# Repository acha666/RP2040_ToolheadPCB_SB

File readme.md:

# Stealthburner_Toolhead_PCB

<font size=5>[中文文档/Chinese Document](readme_cn.md)</font>

## Overview
This project contains a 3Dprinter Toolhead PCB for VORON StealthBurner Toolhead

The board has

* RP2040 Microcontroller, connect to Raspberry PI with USB
* TMC2209 for extruder motor
* MAX31865 RTD-to-Digital Converter
* Si7021/HTU21D humidity&temperature sensor
* ADXL345 accrometer
* Two 5pins fan connecter, fit with 2/3/4 wires, 12/24V fans
* A 3pins probe connecter
* A normal NTC Thermistor connector
* A 2pins X Endstop connector
* A 3pins 5V WS2812(Neopixel) LED connector
* A 24V heater connector

## [Config Referencce](klipper_config.cfg)

## [Programming Guide](Document/programming.md)

## Details
### Microcontroller
You can easily buy a RP2040 chip by about 1USD, it's much cheaper than similar STM32 series MCU today

the RP2040 has some UART interfaces and a USB port, the USB is used for this design

### MAX31865
the on-board MAX31865 chip supports 2/3/4 wires, PT100/PT1000 RTD. please notice that you should choose the reference resistor(430R/4.3K) and a capacitor(100nF/1uF) based on your RTD value. If you use an 3wire RTD, please connect the FORCE2 pin to PORCE+, otherwise connect it to GND. Please make sure that your wiring is correct. Check the [Datasheet](https://datasheets.maximintegrated.com/en/ds/MAX31865.pdf) and [Here](Document/max31865.md) for more information.

### Si7021
This sensor is used to monitor chamber temp.

DS18B20 sensors are only supported on the "host mcu". A NTC thermistor should work too, so if a RTD sensor is used to measure hotend temp, you can have a try.

### ADXL345
is for resonances measurement. Both ADXL343 and ADXL345 should work

### FAN Connecter
support 2wires, 3wires(with speed monitor pin), 4wires(with PWM input and speed monitor)

12V/24V voltage can be set by the jumper. Check [Here](Document/fan.md) for more information.

If using 12V fan, be careful that the current required by the fan must not exceed the maximum current that the DC-DC can provide.

### Neopixel LED
The 5V on the board is the LDO output, the output current is limited, and too many lamp beads cannot be connected in series.

### Heater
be careful about selection on MOSFET, a N-Channel MOSFET with low RDSon at 4.5V

### DC-DC
many models can be used, as long as they have same pin out

The inductor is 4x4mm package, as slim as possible(under 2mm height)

**Inductor Options**
* WPN4012H (Sunlord)
* SPH4012S PH4018 (Sunlord)
* SWPA4010 SWPA4018 SWPA4020 (Sunlord)
* SLW4010 (Sunltech)
* FHD4012 (cjiang)

**Buck converter options**
* LMR14006
* LMR14010
* LMR54410(not tested)
* MP2451(not tested)
* ~~BL9342(not recommended)~~

please check the schmatic and chip datasheet for more details

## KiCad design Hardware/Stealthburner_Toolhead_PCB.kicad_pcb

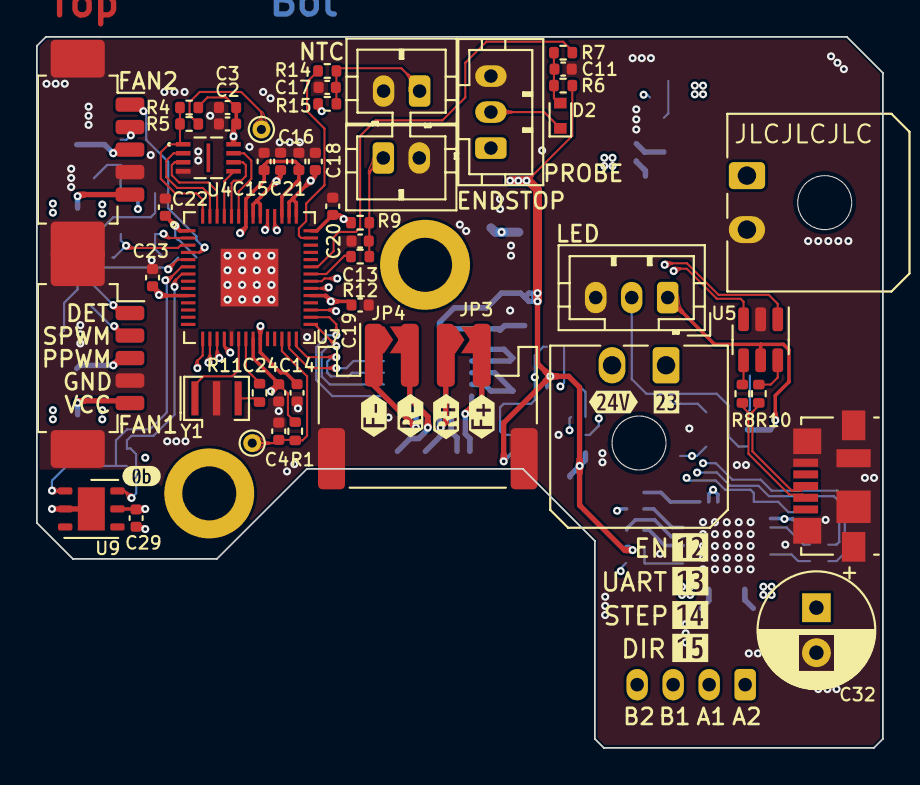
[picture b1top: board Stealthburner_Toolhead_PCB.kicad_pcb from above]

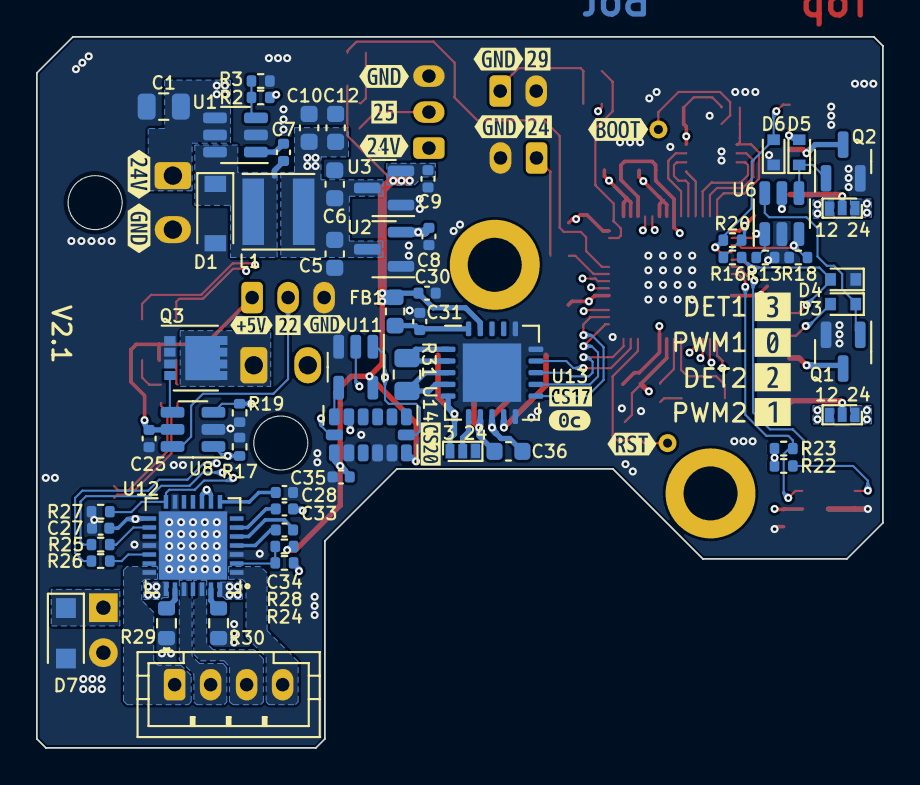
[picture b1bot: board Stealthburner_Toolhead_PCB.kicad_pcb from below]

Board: 4 copper layers, 47.0 x 39.5 mm, 143 parts (80 on the bottom side), 83 nets.

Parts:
C1: 22uF/35V; C_0805_2012Metric
C2: 2.2uF; C_0402_1005Metric
C3, C4, C7, C11, C13, C14, C15, C19, C20, C21, C22, C23, C24, C25, C27, C29, C30, C31, C33, C35: 100nF; C_0402_1005Metric
C5, C6: 10uF; C_0603_1608Metric
C8, C9, C17: 10uF; C_0402_1005Metric
C10, C12: 22uF; C_0603_1608Metric
C16, C18: 1uF; C_0402_1005Metric
C28: 4.7uF; C_0402_1005Metric
C32: 100uF; CP_Radial_D6.3mm_P2.50mm
C34: 22nF; C_0402_1005Metric
C36: 100nF/1uF; C_0603_1608Metric
D1: SS14L; D_SOD-123
D2: 1N4148WT; D_SOD-523
D3, D5: 1N4148; D_SOD-523
D4, D6: D_TVS; D_SOD-523
D7: SMF28A; D_SOD-123F
FB1: 120R@100MHz; L_0603_1608Metric
H1, H2: MountingHole; MountingHole_3mm_Pad
J1, J9: Conn_01x02; Molex_Micro-Fit_3.0_43650-0200_1x02_P3.00mm_Horizontal
J2, J8: Conn_01x03; JST_PH_B3B-PH-K_1x03_P2.00mm_Vertical
J3: TestPoint; TestPoint_THTPad_D1.0mm_Drill0.5mm
J4, J6: Conn_01x02; JST_PH_B2B-PH-K_1x02_P2.00mm_Vertical
J5: USB_B_Micro; USB_Micro-B_Molex_47346-0001
J7, J10: Conn_01x05; Molex_PicoBlade_53261-0571_1x05-1MP_P1.25mm_Horizontal
J11: Conn_01x04; JST_PH_S4B-PH-SM4-TB_1x04-1MP_P2.00mm_Horizontal
J12: Conn_01x04; JST_PH_B4B-PH-K_1x04_P2.00mm_Vertical
JP1, JP2: SolderJumper_3_Open; SolderJumper-3_P1.3mm_Open_Pad1.0x1.5mm
JP3, JP4: SolderJumper_2_Open; SolderJumper-2_P1.3mm_Open_TrianglePad1.0x1.5mm
JP5: 1_Library:SolderJumper-3_P1.3mm_Open_Pad1.0x1.5mm; SolderJumper-3_P1.3mm_Open_Pad1.0x1.5mm
L1: 6.2uH; L_Taiyo-Yuden_NR-40xx
Q1, Q2: AO3400A; SOT-23
Q3: WSD4038DN; VSON-8_3.3x3.3mm_P0.65mm_NexFET
R1, R6, R9, R13, R16, R17, R18, R19, R20, R22, R23: 10K; R_0402_1005Metric
R2: 309K; R_0402_1005Metric
R3: 22.1K; R_0402_1005Metric
R4: NC; R_0402_1005Metric
R5, R11: 1K; R_0402_1005Metric
R7, R12, R14, R24, R25, R26: 100R; R_0402_1005Metric
R8, R10: 27R; R_0402_1005Metric
R15: 4.7K; R_0402_1005Metric
R27, R28: 20K; R_0402_1005Metric
R29, R30: 0R11; R_0603_1608Metric
R31: 430R/4.3K; R_0805_2012Metric
TP1: TestPoint; TestPoint_THTPad_D1.0mm_Drill0.5mm
U1: LMR54410; SOT-23-6
U2: ME6209A50M3G; SOT-23
U3: ME6209A33M3G; SOT-23
U4: W25Q16JVUXIQ_WIN; W25Q16JVUXIQ
U5: USBLC6-2SC6; SOT-23-6
U6, U8: 74LVC2G17; SOT-23-6
U7: RP2040; RP2040TR7
U9: Si7021-A20; DFN-6-1EP_3x3mm_P1mm_EP1.5x2.4mm
U11: 74LVC1G32; SOT-23-5
U12: QFN28_5X5_3X8_EPAD_TRI; TMC2209-LA-T
U13: MAX31865xTP; TQFN-20-1EP_5x5mm_P0.65mm_EP3.25x3.25mm
U14: ADXL343; LGA-14_3x5mm_P0.8mm_LayoutBorder1x6y
Y1: CSTNE12M0; Resonator_SMD_Murata_CSTxExxV-3Pin_3.0x1.1mm
kibuzzard-62BB1C3A: G***; kibuzzard-62BB1C3A
kibuzzard-62BB1DD3: G***; kibuzzard-62BB1DD3
kibuzzard-62BB1FE0: G***; kibuzzard-62BB1FE0
kibuzzard-62BB1FE5: G***; kibuzzard-62BB1FE5
kibuzzard-62BB1FE8: G***; kibuzzard-62BB1FE8
kibuzzard-62BB1FEC: G***; kibuzzard-62BB1FEC
kibuzzard-62BB2156: G***; kibuzzard-62BB2156
kibuzzard-62BB2169: G***; kibuzzard-62BB2169
kibuzzard-62BB2226, kibuzzard-62BB2226#2, kibuzzard-62BB2226#3: G***; kibuzzard-62BB2226
kibuzzard-62BB2232, kibuzzard-62BB2232#2, kibuzzard-62BB2232#3, kibuzzard-62BB2232#4: G***; kibuzzard-62BB2232
kibuzzard-62BB2280: G***; kibuzzard-62BB2280
kibuzzard-62BD8A5A: G***; kibuzzard-62BD8A5A
kibuzzard-62BD8A5E: G***; kibuzzard-62BD8A5E
kibuzzard-62BD8A50: G***; kibuzzard-62BD8A50
kibuzzard-62BD8A57: G***; kibuzzard-62BD8A57
kibuzzard-62BD8C8D: G***; kibuzzard-62BD8C8D
kibuzzard-62BD8C64: G***; kibuzzard-62BD8C64
kibuzzard-62BD8846: G***; kibuzzard-62BD8846
kibuzzard-62E7C93B: G***; kibuzzard-62E7C93B
kibuzzard-62E7C936: G***; kibuzzard-62E7C936
kibuzzard-62E7C943: G***; kibuzzard-62E7C943
kibuzzard-62E7C964: G***; kibuzzard-62E7C964
kibuzzard-62F0BBF4: G***; kibuzzard-62F0BBF4
kibuzzard-6309F118: G***; kibuzzard-6309F118
kibuzzard-63148E7F: G***; kibuzzard-63148E7F
kibuzzard-63148E89: G***; kibuzzard-63148E89
kibuzzard-63148E96: G***; kibuzzard-63148E96

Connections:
+1V1: C14.1, C15.1, C16.1, U7.23 (DVDD), U7.45 (VREG_VOUT), U7.50 (DVDD)
+3V3: C2.1, C3.1, C9.1, C18.1, C19.1, C20.1, C21.1, C22.1, C23.1, C24.1, C27.2, C29.1, C30.1, C35.1, FB1.1, R1.1, R4.1, R6.1, R9.1, R15.1, R16.1, R20.1, R22.1, R23.1, R28.1, U3.2 (OUT), U4.8 (VCC), U7.1 (IOVDD), U7.10 (IOVDD), U7.22 (IOVDD), U7.33 (IOVDD), U7.42 (IOVDD), U7.43 (ADC_AVDD), U7.44 (VREG_IN), U7.48 (USB_VDD), U7.49 (IOVDD), U9.5 (VDD), U11.5 (VCC), U12.9 (MS1_AD0), U12.10 (MS2_AD1), U12.15 (VCC_IO), U13.19 (DVDD), U14.1 (Vdd_I/O), U14.6 (Vs)
+5V: C8.1, C25.2, J8.1, U2.2 (OUT), U5.5 (VBUS), U6.5 (VCC), U8.5 (VCC)
+12V: C5.1, C6.1, C10.1, C12.1, JP1.3 (B), JP2.3 (B), L1.2, R2.1, U2.3 (IN), U3.3 (IN)
+24V: C1.1, C32.1, C33.2, D7.1 (A1), J1.1, J2.1, J9.2, JP1.1 (A), JP2.1 (A), U1.4 (EN), U1.5 (VIN), U12.22 (VS), U12.28 (VS)
/D+: U5.1 (I/O1), U7.47 (USB_DP)
/D-: U5.3 (I/O2), U7.46 (USB_DM)
/E-A1: J12.2, U12.24 (OA1)
/E-A2: J12.1, U12.21 (OA2)
/E-B1: J12.3, U12.26 (OB1)
/E-B2: J12.4, U12.1 (OB2)
/E-DIR: R26.1, U7.18 (GPIO15)
/E-EN: R24.1, U7.15 (GPIO12)
/E-STEP: R25.1, U7.17 (GPIO14)
/FAN1_DET: D4.2 (A2), J7.1, R16.2, U7.5 (GPIO3)
/FAN1_PWM: R13.1, U6.1, U7.2 (GPIO0)
/FAN2_DET: D6.2 (A2), J10.1, R20.2, U7.4 (GPIO2)
/FAN2_PWM: R18.1, U6.3, U7.3 (GPIO1)
/FORCE2: JP5.2 (C), U13.6 (FORCE2)
/FORCE+: J11.4, JP3.2 (B), JP5.1 (A), U13.5 (FORCE+)
/FORCE-: J11.1, JP4.1 (A), U13.9 (FORCE-)
/HE: R19.1, U7.35 (GPIO23), U8.3
/IIC0_SCL: R23.2, U7.7 (GPIO5), U9.6 (SCL)
/IIC0_SDA: R22.2, U7.6 (GPIO4), U9.1 (SDA)
/NEO: R17.1, U7.34 (GPIO22), U8.1
/NTC: R14.1, U7.41 (GPIO29_ADC3)
/PROBE: R7.1, U7.37 (GPIO25)
/QSPI_CLK: U4.6 (CLK), U7.52 (QSPI_SCLK)
/QSPI_CS: R4.2, R5.2, U4.1 (~CS), U7.56 (QSPI_SS)
/QSPI_SD0: U4.5 (DI_IO0), U7.53 (QSPI_SD0)
/QSPI_SD1: U4.2 (DO_IO1), U7.55 (QSPI_SD1)
/QSPI_SD2: U4.3 (~WP_IO2), U7.54 (QSPI_SD2)
/QSPI_SD3: U4.7 (~HOLD_IO3), U7.51 (QSPI_SD3)
/RTDIN+: C36.1, J11.3, JP3.1 (A), U13.7 (RTDIN+)
/RTDIN-: C36.2, J11.2, JP4.2 (B), U13.8 (RTDIN-)
/RUN: C4.1, R1.2, TP1.1, U7.26 (RUN)
/SPI0_CLK: U7.29 (GPIO18), U13.12 (SCLK), U14.14 (SCL/SCLK)
/SPI0_CS1: U7.28 (GPIO17), U13.13 (~CS)
/SPI0_CS2: U7.31 (GPIO20), U11.1, U14.7 (~CS)
/SPI0_MISO: U7.27 (GPIO16), U13.14 (SDO), U14.12 (SDO/ADDR)
/SPI0_MOSI: U7.30 (GPIO19), U11.2, U13.11 (SDI)
/UART: R27.2, U7.16 (GPIO13), U12.14 (PDN_UART)
/X-: R12.1, U7.36 (GPIO24)
GND: C1.2, C2.2, C3.2, C4.2, C5.2, C6.2, C8.2, C9.2, C10.2, C11.2, C12.2, C13.2, C14.2, C15.2, C16.2, C17.2, C18.2, C19.2, C20.2, C21.2, C22.2, C23.2, C24.2, C25.1, C27.1, C28.1, C29.2, C30.2, C31.2, C32.2, C35.2, D1.2 (A), D4.1 (A1), D6.1 (A1), D7.2 (A2), J1.2, J2.3, J4.2, J5.5 (GND), J5.6 (Shield), J6.2, J7.4, J7.MP (MountPin), J8.3, J10.4, J10.MP (MountPin), J11.MP (MountPin), JP5.3 (B), Q1.2 (S), Q2.2 (S), Q3.1 (S), Q3.2 (S), Q3.3 (S), R3.2, R13.2, R17.2, R18.2, R19.2, R27.1, R29.2, R30.2, U1.2 (GND), U2.1 (GND), U3.1 (GND), U4.4 (GND), U5.2 (GND), U6.2 (GND), U7.19 (TESTEN), U7.57 (GND), U8.2 (GND), U9.2 (GND), U9.7 (PAD), U11.3 (GND), U12.3 (GND), U12.13 (CLK), U12.18 (GND), U12.29 (EPAD), U13.10 (GND), U13.15 (DGND), U13.16 (GND), U13.21 (GND), U14.2 (GND), U14.4 (GND), U14.5 (GND), Y1.2
unnamed: C7.1, D1.1 (K), L1.1, U1.6 (SW)
unnamed: C7.2, U1.1 (CB)
unnamed: C11.1, D2.2 (A), R6.2, R7.2
unnamed: C13.1, J4.1, R9.2, R12.2
unnamed: C17.1, J6.1, R14.2, R15.2
unnamed: C28.2, U12.8 (5VOUT)
unnamed: C31.1, FB1.2, U13.20 (VDD)
unnamed: C33.1, U12.6 (VCP)
unnamed: C34.1, U12.4 (CPO)
unnamed: C34.2, U12.5 (CPI)
unnamed: D2.1 (K), J2.2
unnamed: D3.1 (K), Q1.1 (G), U6.6
unnamed: D3.2 (A), J7.2
unnamed: D5.1 (K), Q2.1 (G), U6.4
unnamed: D5.2 (A), J10.2
unnamed: J3.1, R5.1
unnamed: J5.2 (D-), R8.2
unnamed: J5.3 (D+), R10.1
unnamed: J7.3, Q1.3 (D)
unnamed: J7.5, JP1.2 (C)
unnamed: J8.2, U8.6
unnamed: J9.1, Q3.5 (D)
unnamed: J10.3, Q2.3 (D)
unnamed: J10.5, JP2.2 (C)
unnamed: Q3.4 (G), U8.4
unnamed: R2.2, R3.1, U1.3 (FB)
unnamed: R8.1, U5.4 (I/O2)
unnamed: R10.2, U5.6 (I/O1)
unnamed: R11.1, U7.21 (XOUT)
unnamed: R11.2, Y1.3
unnamed: R24.2, R28.2, U12.2 (ENN)
unnamed: R25.2, U12.16 (STEP)
unnamed: R26.2, U12.19 (DIR)
unnamed: R29.1, U12.23 (BRA)
unnamed: R30.1, U12.27 (BRB)
unnamed: R31.1, U13.1 (BIAS), U13.2 (REFIN+)
unnamed: R31.2, U13.3 (REFIN-), U13.4 (ISENSOR)
unnamed: U7.20 (XIN), Y1.1
unnamed: U11.4, U14.13 (SDA/SDI/SDIO)

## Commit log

2022-06-29 2nd commit
2022-06-30 Create LICENSE
2022-07-03 REV1.0
2022-07-26 document changes
2022-08-02 V1.1 Release
    * Add a TVS for TMC2209
    * Replaced SHT21 with Si7021
2022-08-08 bugs fix
2022-08-27 V1.2 Release
    *Changelog*
    * 略微修改PCB尺寸与原件布局，防止板子与打印件干涉
    * 删除了温度传感器周围的铺铜
    * 修复一些小bug
2022-09-20 V2.1 Replace Molex PicoBlade Connector with PH2.0 Connector Replace USB connector with Micro USB port Modified PCB size
    将1.25mm连接器替换为2.0mm
    使用MicroUSB母座作为USB连接器
    修改PCB尺寸
2022-09-25 6Layers Version
    6Layers PCB
2022-10-07 Init
    first commit
2022-10-07 Document Changes
    Document changes
2022-10-07 V2.1 Release
    将1.25mm连接器替换为2.0mm
    使用MicroUSB母座作为USB连接器
    修改PCB尺寸
    Replace Molex PicoBlade Connector with PH2.0 Connector
    Replace USB connector with Micro USB port
    Modified PCB size

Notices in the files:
parts and their libraries:
Copyright 2021 Accelerated Designs. All rights reserved.
